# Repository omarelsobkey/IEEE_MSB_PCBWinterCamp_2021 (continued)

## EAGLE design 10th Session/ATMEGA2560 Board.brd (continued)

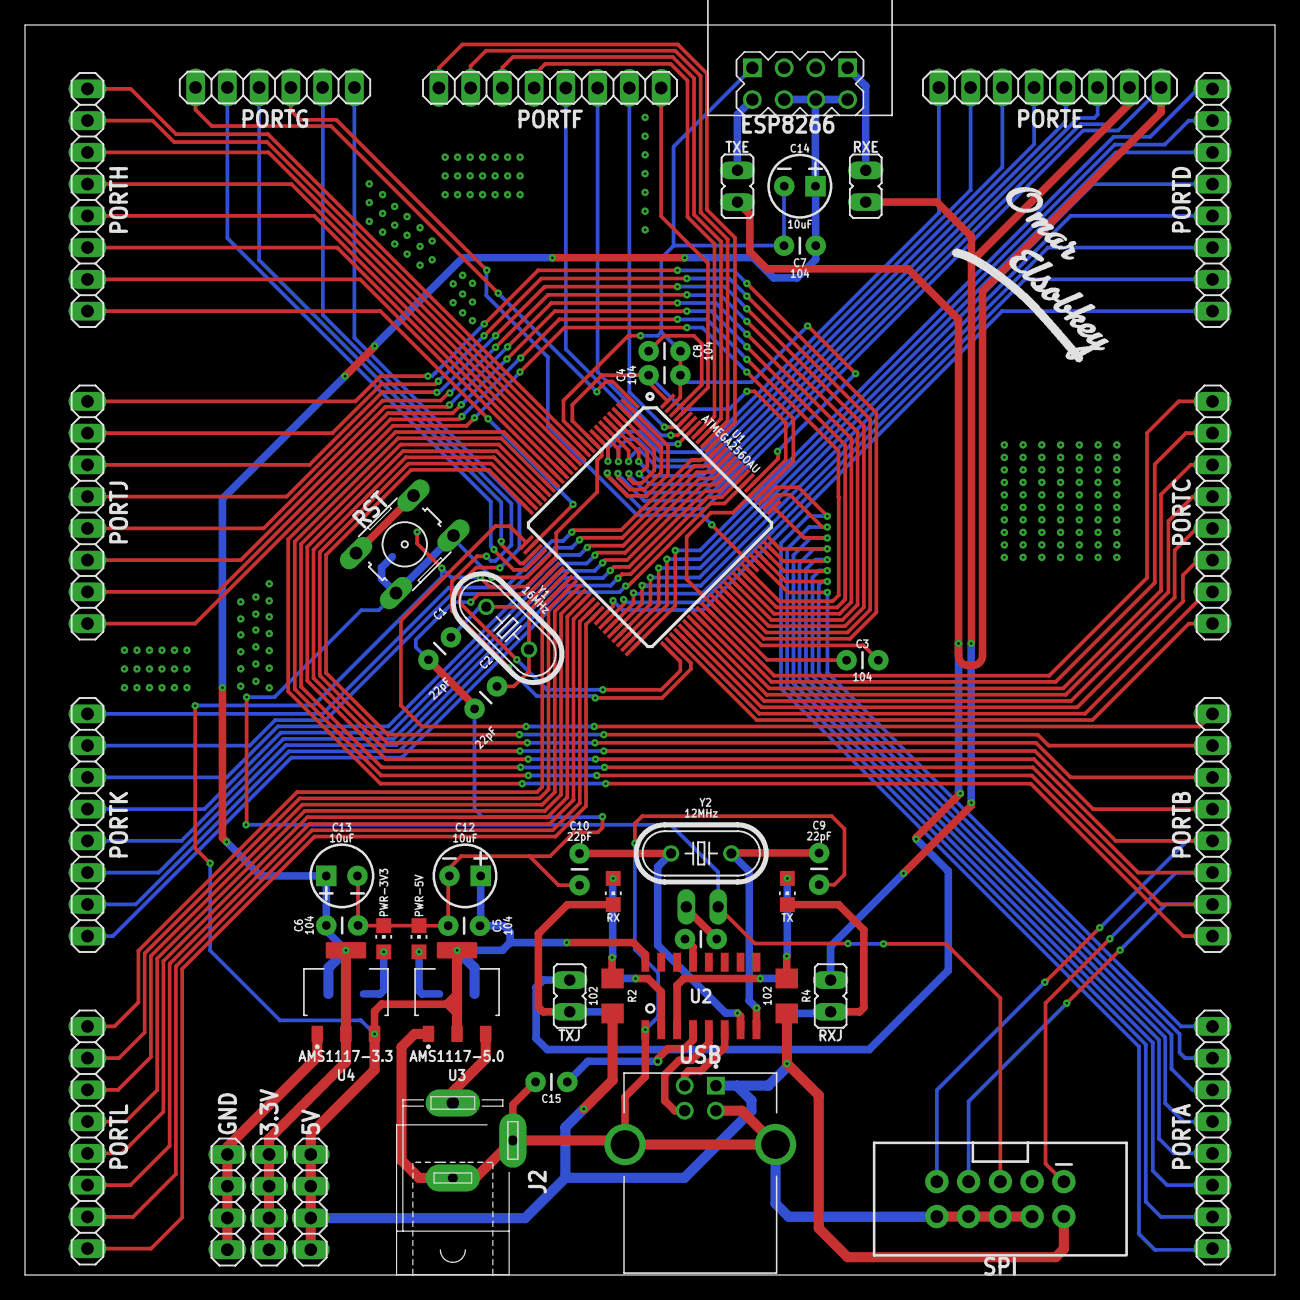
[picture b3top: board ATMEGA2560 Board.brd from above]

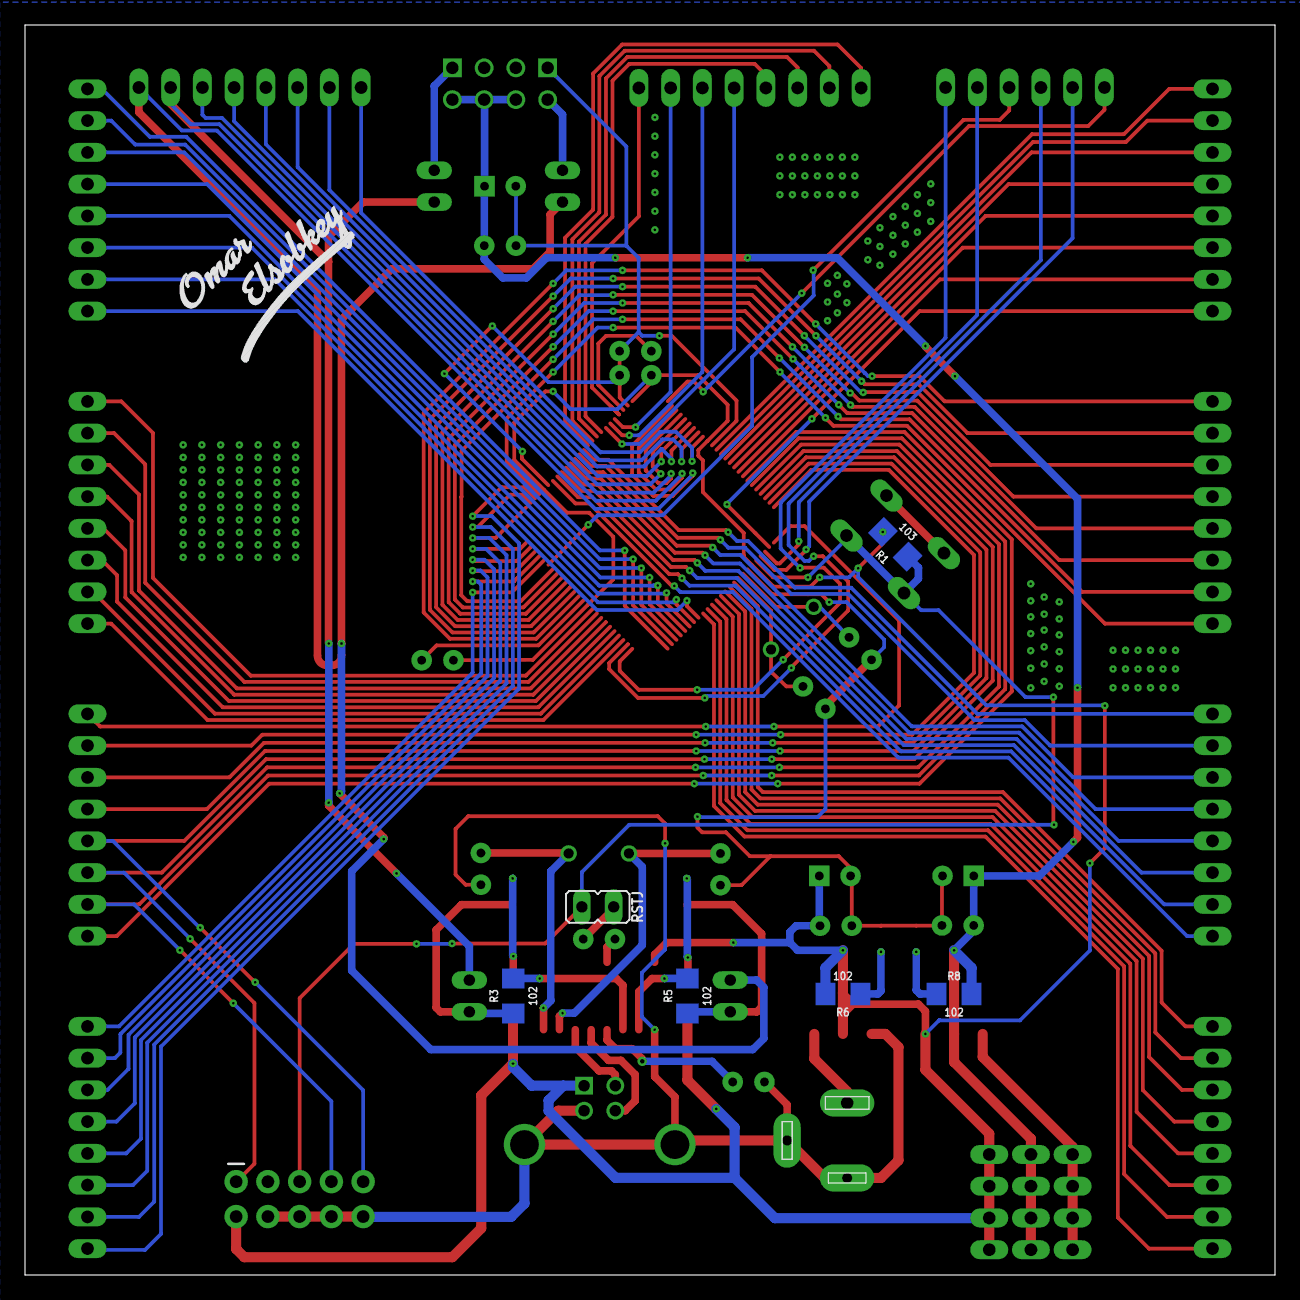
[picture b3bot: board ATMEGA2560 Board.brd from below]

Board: 2 copper layers, 100.0 x 100.0 mm, 58 parts (7 on the bottom side), 111 nets.

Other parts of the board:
U$1, U$2: OMAR_ELSOBKEY_X1

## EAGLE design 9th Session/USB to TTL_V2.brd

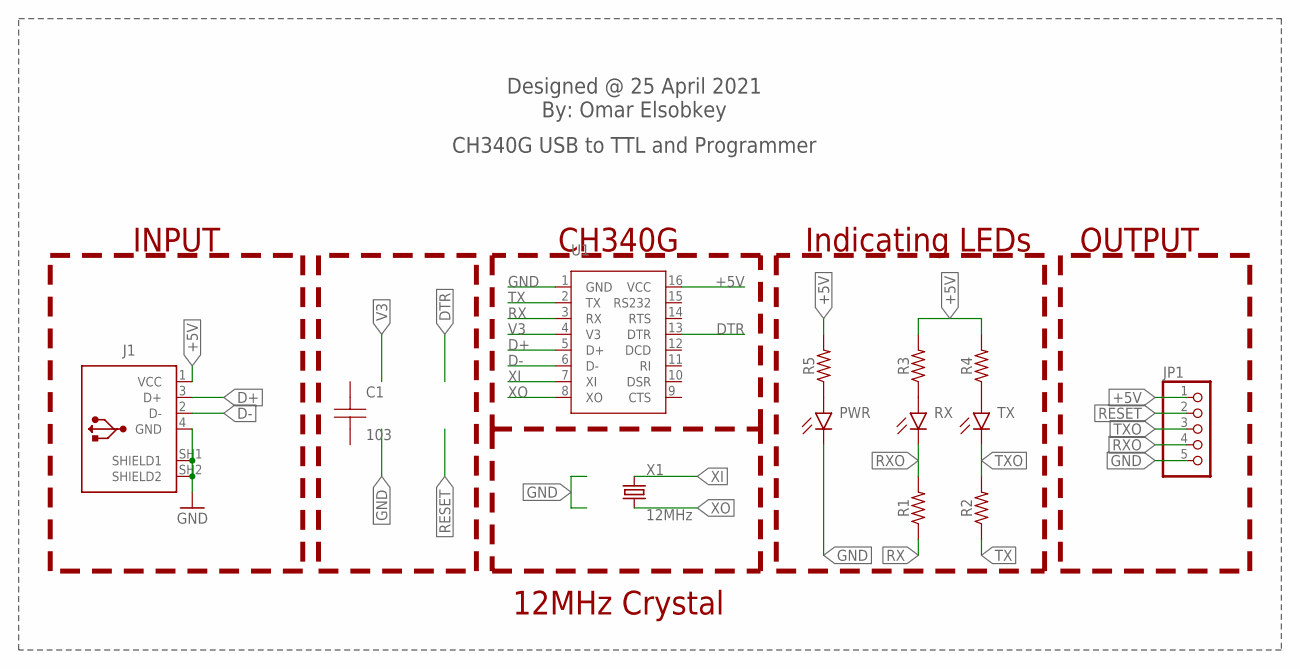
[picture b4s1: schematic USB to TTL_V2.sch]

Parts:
C1: 103; P2.8
J1: 61729-1011; 61729-1011BLF
JP1: PINHD-1X5/90; 1X05/90
PWR: CHIP-FLAT-B_0805; LEDC2012X110N_FLAT-B
R1, R2: 1k; 1206
R3, R4, R5: 102; 1206
RX: CHIP-FLAT-B_0805; LEDC2012X110N_FLAT-B
TX: CHIP-FLAT-B_0805; LEDC2012X110N_FLAT-B
U1: CH340G; SOP-16
X1: 12MHz; XTAL_HC49

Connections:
+5V: J1.1 (VCC), JP1.1, R3.2, R4.2, R5.2, U1.16 (VCC)
D+: J1.3 (D+), U1.5 (D+)
D-: J1.2 (D-), U1.6 (D-)
DTR: U1.13 (DTR)
GND: J1.4 (GND), J1.SH1 (SHIELD1), J1.SH2 (SHIELD2), JP1.5, PWR.C, U1.1 (GND)
unnamed: R3.1, RX.A
unnamed: R4.1, TX.A
unnamed: PWR.A, R5.1
RESET: JP1.2
RX: R1.1, U1.3 (RX)
RXO: JP1.4, R1.2, RX.C
TX: R2.1, U1.2 (TX)
TXO: JP1.3, R2.2, TX.C
V3: U1.4 (V3)
XI: U1.7 (XI), X1.2
XO: U1.8 (XO), X1.1

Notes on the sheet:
Designed @ 25 April 2021 By: Omar Elsobkey
CH340G USB to TTL and Programmer
INPUT
CH340G
12MHz Crystal
Indicating LEDs
OUTPUT

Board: 2 copper layers, 15 parts (1 on the bottom side), 13 nets, no tracks yet.

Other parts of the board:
U$1, U$2: OMAR_ELSOBKEY_X0.5_TN
